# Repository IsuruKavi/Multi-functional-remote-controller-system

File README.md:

🚀 Successfully Designed a Remote Controller System for Wave Soldering Machine 🛠️
During my internship , I had the opportunity to work on an innovative project aimed at enhancing the safety and convenience of wave soldering machine operations. The core objective was to remotely control the hot solder bath, eliminating the need for operators to be in close proximity to the potentially dangerous liquid solder.

**Key Features**:
- I designed and implemented a user-friendly interface with four push buttons (Up, Down, In, Out) to facilitate machine operations.
- Normal operation required a 2-3 minute continuous button press, but I engineered a solution allowing operators to initiate actions with a single button press and stop the operation by pressing again.

**Two Operating Modes**:
- **Manual Mode (Green Light)**: The system defaults to this mode at startup. Operators must press and hold buttons to execute operations.
- **Auto Mode (Red Light)**: In this mode, a single button press triggers and controls the operation. Press "Out" to start, and it can be stopped by pressing "In" or "Out." Additionally, the system includes a safety feature: the relays will automatically turn off after 2.5 minutes, ensuring that even if the operator doesn't manually turn off the operation, safety is maintained.

**Seamless Mode Switching**:
- Users can effortlessly switch between modes by pressing the middle button.

**Technology Stack**:
- I harnessed RF communication with RF modules, encoders, and decoders.
- The project's core is the PIC16F76 microcontroller, enabling precise control and reliable operation.

**Code Implementation**:
-I meticulously crafted robust code for both the transmitter and receiver sides to guarantee error-free signal transmission and reception.
-A critical focus was to ensure the system could maintain control and data integrity during signal interruptions, preventing risky conditions during operations.

**PCB Design and Development**:
- Initially, I assembled the system using a vero board.
- Subsequently, I ventured into PCB design. I'll be sharing photos of the vero board for the transmitter and receiver shortly.

#####_Code,schematic and some photos have been uploaded_#####

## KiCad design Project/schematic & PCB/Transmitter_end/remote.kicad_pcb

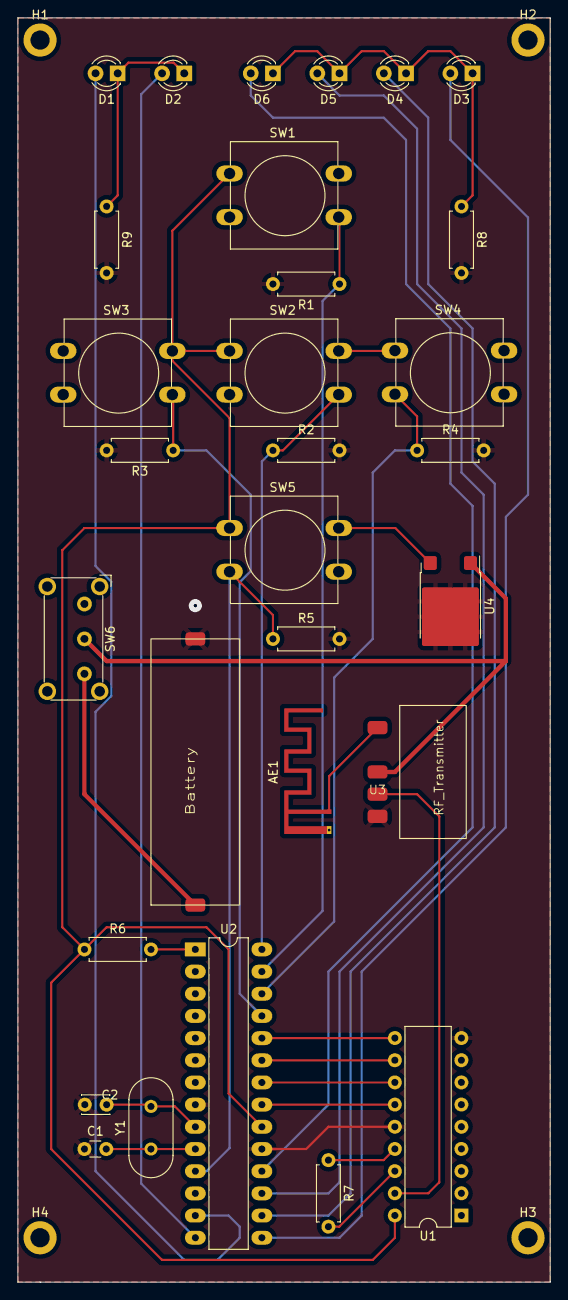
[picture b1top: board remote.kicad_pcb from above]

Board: 2 copper layers, 61.0 x 144.8 mm, 34 parts (0 on the bottom side), 28 nets.

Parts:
AE1: Antenna; Texas_SWRA117D_2.4GHz_Right
BT1: Battery_Cell; battery
C1: C; C_Disc_D3.0mm_W1.6mm_P2.50mm
C2: C; C_Disc_D3.0mm_W2.0mm_P2.50mm
D1, D2, D3, D4, D5, D6: LED; LED_D3.0mm
H1, H2, H3, H4: MountingHole; MountingHole_2.2mm_M2_DIN965_Pad
R1, R2, R3, R4, R5, R6, R7, R8, R9: R; R_Axial_DIN0207_L6.3mm_D2.5mm_P7.62mm_Horizontal
SW1, SW2, SW3, SW4, SW5: SW_Push; SW_PUSH-12mm
SW6: SW_DIP_x01; SW_E-Switch_EG1224_SPDT_Angled
U1: HT12E; DIP-18_W7.62mm
U2: PIC16F76-ISP; DIP-28_W7.62mm_LongPads
U3: rf_tr
U4: L7805; ATPAK-2
Y1: Crystal; Crystal_HC49-4H_Vertical

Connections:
+5V: R6.1, SW1.1, SW2.1, SW3.1, SW4.1, SW5.1, U1.18 (VDD), U2.20 (VDD), U4.3 (OUT)
+12V: BT1.1 (+), SW6.1
GND: BT1.2 (-), C1.1, C2.1, R1.2, R2.2, R3.2, R4.2, R5.2, R8.2, R9.2, U1.9 (VSS), U1.14 (~TE), U2.8 (VSS), U2.19 (VSS), U3.3 (GND), U4.2 (GND)
unnamed: AE1.1 (A), U3.4 (Antenna)
unnamed: D1.2 (A), U2.13 (RC2/CCP1)
unnamed: D1.1 (K), D2.1 (K), R9.1
unnamed: D2.2 (A), U2.14 (RC3/SCK/SCL)
unnamed: D3.2 (A), U2.15 (RC4/SDI/SDA)
unnamed: D3.1 (K), D4.1 (K), D5.1 (K), D6.1 (K), R8.1
unnamed: D4.2 (A), U2.16 (RC5/SDO)
unnamed: D5.2 (A), U2.17 (RC6/TX/CK)
unnamed: D6.2 (A), U2.18 (RC7/RX/DT)
unnamed: U1.10 (AD8), U2.24 (PGM/RB3)
unnamed: U1.11 (AD9), U2.23 (RB2)
unnamed: U1.12 (AD10), U2.22 (RB1)
unnamed: U1.13 (AD11), U2.21 (INT/RB0)
unnamed: U1.17 (DOUT), U3.2 (Data)
unnamed: R7.2, U1.16 (OSC1)
unnamed: R7.1, U1.15 (OSC2)
unnamed: C2.2, U2.9 (OSC1/CLKIN), Y1.2
unnamed: C1.2, U2.10 (OSC2/CLKOUT), Y1.1
unnamed: R1.1, SW1.2, U2.27 (PGC/RB6)
unnamed: R2.1, SW2.2, U2.28 (PGD/RB7)
unnamed: R3.1, SW3.2, U2.25 (RB4)
unnamed: R4.1, SW4.2, U2.26 (RB5)
unnamed: R5.1, SW5.2, U2.11 (RC0/T10S0/T1CKI)
unnamed: R6.2, U2.1 (~MCLR/Vpp)
unnamed: SW6.2, U3.1 (Vcc), U4.1 (IN)

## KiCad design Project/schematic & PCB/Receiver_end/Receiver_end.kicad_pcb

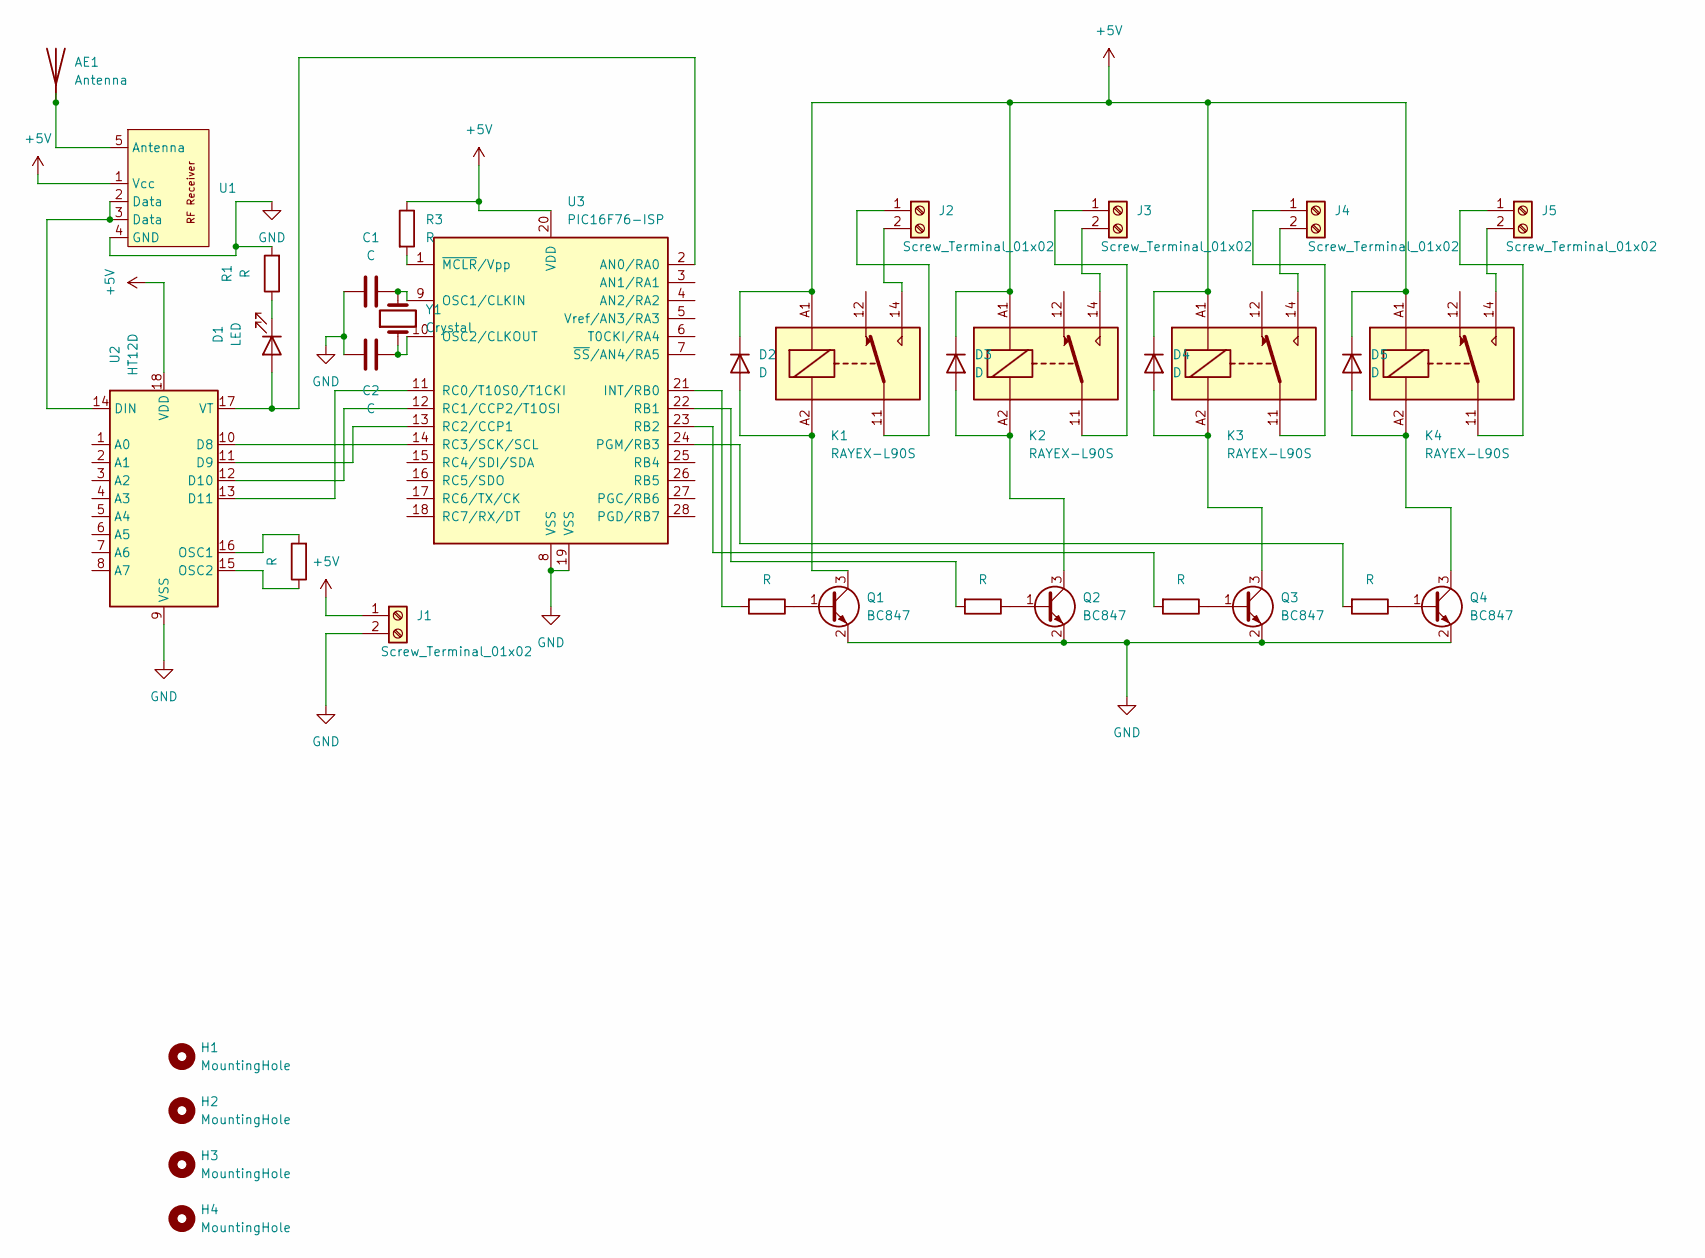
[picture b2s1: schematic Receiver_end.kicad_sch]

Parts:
AE1: Antenna; Texas_SWRA117D_2.4GHz_Right
C1, C2: C; C_Disc_D3.4mm_W2.1mm_P2.50mm
D1: LED; LED_D3.0mm
D2, D3, D4, D5: D; D_TUMD2
H1, H2, H3, H4: MountingHole; MountingHole_2.2mm_M2_DIN965_Pad
J1, J2, J3, J4, J5: Screw_Terminal_01x02; TerminalBlock_Phoenix_MKDS-1,5-2_1x02_P5.00mm_Horizontal
K1, K2, K3, K4: RAYEX-L90S; Relay_1-Form-C_Schrack-RYII_RM3.2mm
Q1, Q2, Q3, Q4: BC847; SOT-23
R1, R2, R3: R; R_Axial_DIN0207_L6.3mm_D2.5mm_P7.62mm_Horizontal
R4, R5, R6, R7: R; R_0603_1608Metric
U1: receiver footprint
U2: HT12D; DIP-18_W7.62mm_LongPads
U3: PIC16F76-ISP; DIP-28_W7.62mm
Y1: Crystal; Crystal_HC49-4H_Vertical

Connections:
+5V: D2.1 (K), D3.1 (K), D4.1 (K), D5.1 (K), J1.1, K1.A1, K2.A1, K3.A1, K4.A1, R3.1, U1.1 (Vcc), U2.18 (VDD), U3.20 (VDD)
GND: C1.1, C2.1, J1.2, Q1.2 (E), Q2.2 (E), Q3.2 (E), Q4.2 (E), R1.2, U1.4 (GND), U2.9 (VSS), U3.8 (VSS), U3.19 (VSS)
unnamed: AE1.1 (A), U1.5 (Antenna)
unnamed: D1.2 (A), U2.17 (VT), U3.2 (AN0/RA0)
unnamed: D1.1 (K), R1.1
unnamed: D2.2 (A), K1.A2, Q1.3 (C)
unnamed: D3.2 (A), K2.A2, Q2.3 (C)
unnamed: D4.2 (A), K3.A2, Q3.3 (C)
unnamed: D5.2 (A), K4.A2, Q4.3 (C)
unnamed: J2.1, K1.11
unnamed: J2.2, K1.14
unnamed: J3.1, K2.11
unnamed: J3.2, K2.14
unnamed: J4.1, K3.11
unnamed: J4.2, K3.14
unnamed: J5.1, K4.11
unnamed: J5.2, K4.14
unnamed: Q1.1 (B), R4.1
unnamed: Q2.1 (B), R5.1
unnamed: Q3.1 (B), R6.1
unnamed: Q4.1 (B), R7.1
unnamed: U2.10 (D8), U3.14 (RC3/SCK/SCL)
unnamed: U2.11 (D9), U3.13 (RC2/CCP1)
unnamed: U2.12 (D10), U3.12 (RC1/CCP2/T1OSI)
unnamed: U2.13 (D11), U3.11 (RC0/T10S0/T1CKI)
unnamed: U1.2 (Data), U1.3 (Data), U2.14 (DIN)
unnamed: R2.2, U2.16 (OSC1)
unnamed: R2.1, U2.15 (OSC2)
unnamed: R4.2, U3.21 (INT/RB0)
unnamed: C1.2, U3.9 (OSC1/CLKIN), Y1.2
unnamed: C2.2, U3.10 (OSC2/CLKOUT), Y1.1
unnamed: R7.2, U3.24 (PGM/RB3)
unnamed: R5.2, U3.22 (RB1)
unnamed: R6.2, U3.23 (RB2)
unnamed: R3.2, U3.1 (~MCLR/Vpp)

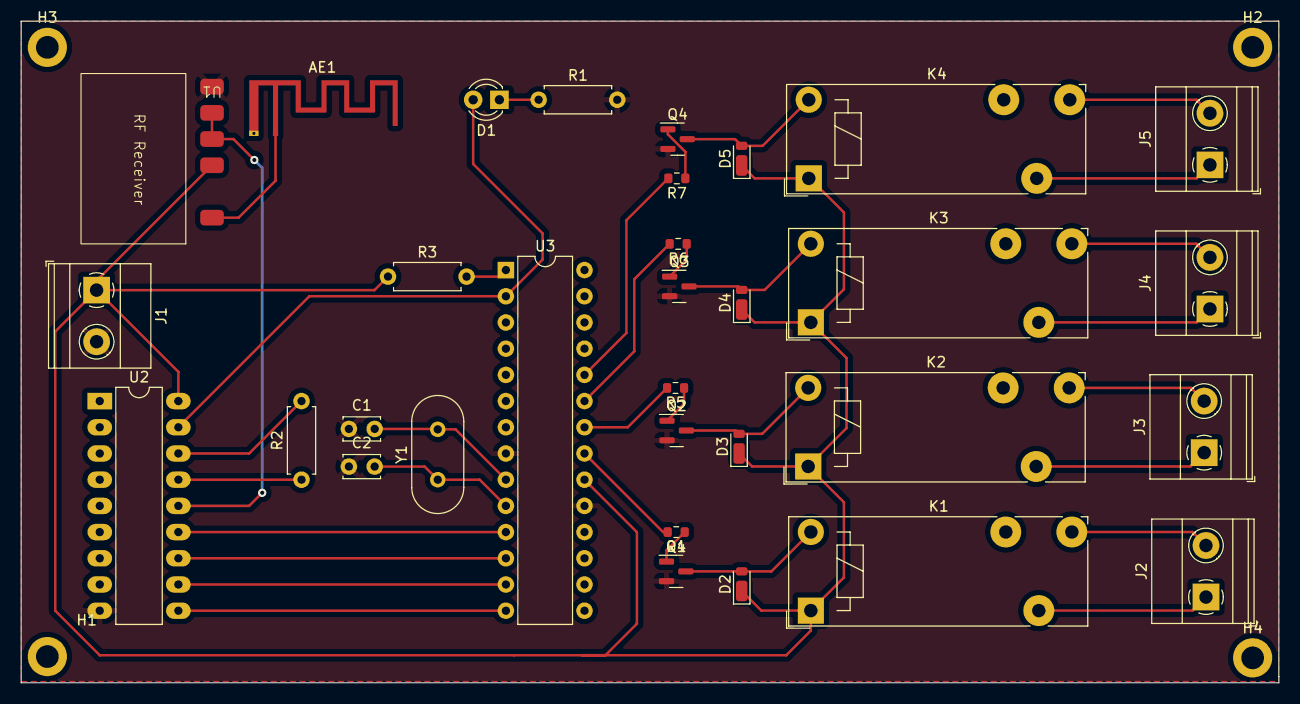
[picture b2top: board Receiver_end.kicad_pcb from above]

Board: 2 copper layers, 121.9 x 64.1 mm, 36 parts (0 on the bottom side), 35 nets.

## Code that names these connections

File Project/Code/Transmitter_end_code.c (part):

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#define _XTAL_FREQ 16000000
#include <xc.h>
//OUTPUTS
#define LED1        PORTCbits.RC2
#define LED2        PORTCbits.RC3
#define Out_relay   PORTBbits.RB2
#define In_relay    PORTBbits.RB3
#define Down_relay  PORTBbits.RB1
#define Up_relay    PORTBbits.RB0
#define LED_OUT      PORTCbits.RC6
#define LED_IN       PORTCbits.RC7
#define LED_DOWN      PORTCbits.RC5
#define LED_UP        PORTCbits.RC4

//INPUTS

#define Pb PORTBbits.RB6
#define Out_button PORTBbits.RB7
#define In_button PORTBbits.RB4
#define Down_button PORTBbits.RB5
#define Up_button PORTCbits.RC0

void main(void) {
    // Outputs
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
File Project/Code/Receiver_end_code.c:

/// PIC16F76 Configuration Bit Settings
// 'C' source line config statements
// CONFIG
#pragma config FOSC = HS        // Oscillator Selection bits (HS oscillator)
#pragma config WDTE = OFF       // Watchdog Timer Enable bit (WDT disabled)
#pragma config PWRTE = OFF      // Power-up Timer Enable bit (PWRT disabled)
#pragma config CP = OFF         // FLASH Program Memory Code Protection bit (Code protection off)
#pragma config BOREN = ON       // Brown-out Reset Enable bit (BOR enabled)

// #pragma config statements should precede project file includes.
// Use project enums instead of #define for ON and OFF.

#define _XTAL_FREQ 16000000
#include <xc.h>
//OUTPUTS

#define Out_relay   PORTBbits.RB3
#define In_relay    PORTBbits.RB2
#define Down_relay  PORTBbits.RB1
#define Up_relay    PORTBbits.RB0

//INPUTS

#define Transmission_enable PORTAbits.RA0
#define Out_button PORTCbits.RC0
#define In_button PORTCbits.RC1
#define Down_button PORTCbits.RC2
#define Up_button PORTCbits.RC3

void main(void) {
    // Outputs
    TRISBbits.TRISB0 = 0;
    TRISBbits.TRISB1 = 0;
    TRISBbits.TRISB2 = 0;
    TRISBbits.TRISB3= 0;
    

    // Inputs
    TRISCbits.TRISC0 = 1;
    TRISCbits.TRISC1 = 1;
    TRISCbits.TRISC2 = 1;
    TRISCbits.TRISC3 = 1;
    TRISAbits.TRISA0 = 1;
    
    In_relay=1;
    Out_relay=1;
    Up_relay=1;
    Down_relay=1; 
    __delay_ms(100);

    while (1) {
        //code for turning of relays when signal isn't received for 400ms 
        if(Transmission_enable==0 ){
            for(int t=0; t<=8; t++){
                    __delay_ms(50);
                    if(Transmission_enable==1){
                        break;
                    }
                    else if(t==8){
                        Up_relay=1;
                        Down_relay=1;
                        In_relay=1;
                        Out_relay=1;
                         }
                    
                }
        }//code to operate the relays.
        else{
         if(Up_button==1 && Down_button==0 && In_button==0 && Out_button==0){
           
            Up_relay=0;
                
        }
        if(Up_button==0){
            Up_relay=1;
            
        }
        if(Down_button==1 && Up_button==0 && In_button==0 && Out_button==0){
            
            Down_relay=0;
                
        }if(Down_button==0){
            Down_relay=1;
        }
        
        if(In_button==1 && Down_button==0 && Up_button==0 && Out_button==0){
           
            In_relay=0;
           
        }if(In_button==0){
            In_relay=1;
        
        }
        if(Out_button==1 &&  Down_button==0 && In_button==0 && Up_button==0){
            
            Out_relay=0;
            
        }if(Out_button==0){
            Out_relay=1;
        }
        
        }
        
    } }
